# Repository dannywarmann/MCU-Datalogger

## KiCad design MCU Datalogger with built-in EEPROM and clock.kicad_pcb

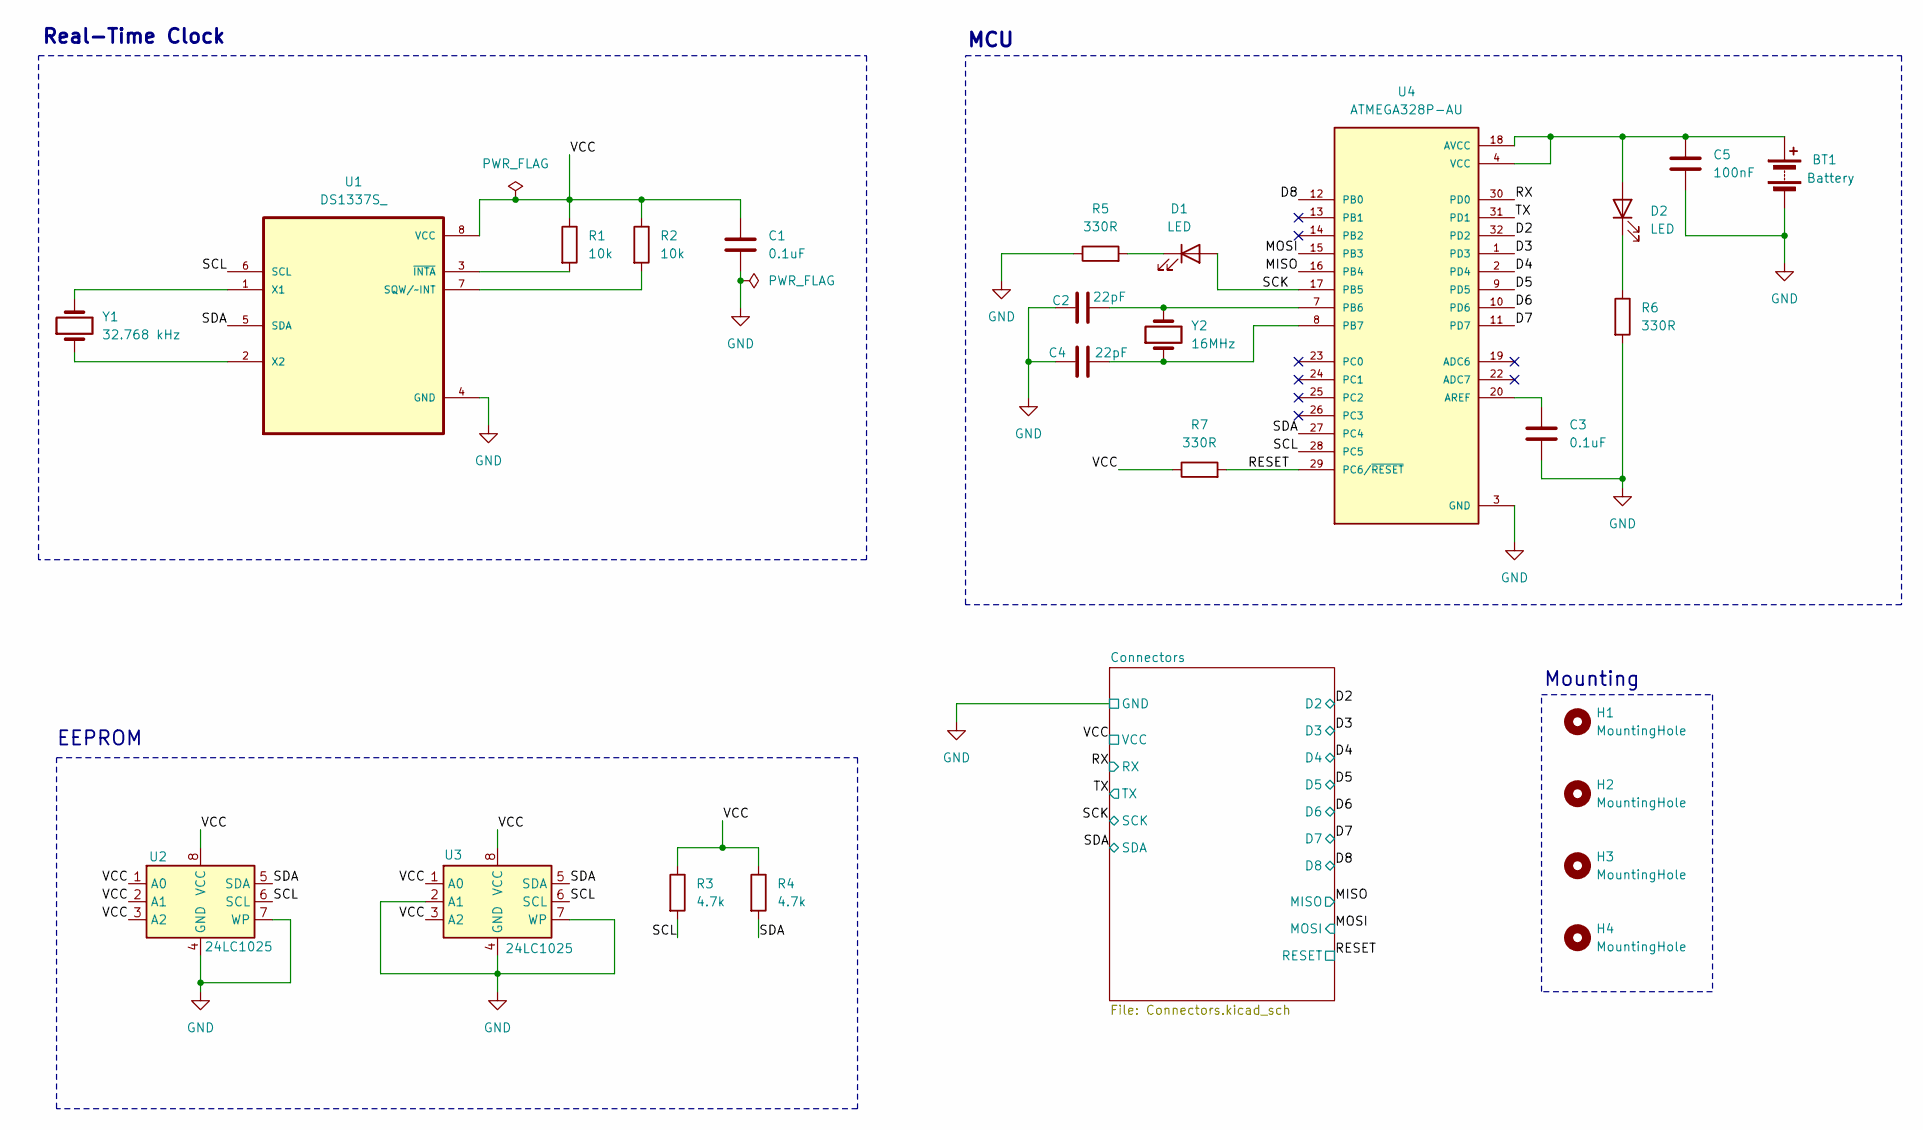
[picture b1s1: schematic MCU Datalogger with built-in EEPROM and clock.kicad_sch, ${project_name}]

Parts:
BT1: Battery; PinHeader_1x02_P2.54mm_Vertical
C1, C3: 0.1uF; C_0805_2012Metric
C2, C4: 22pF; C_0805_2012Metric
C5: 100nF; C_0805_2012Metric
D1, D2: LED; LED_0805_2012Metric
H1, H2, H3, H4: MountingHole; MountingHole_2.1mm
R1, R2: 10k; R_0805_2012Metric
R3, R4: 4.7k; R_0805_2012Metric
R5, R6, R7: 330R; R_0805_2012Metric
U1: DS1337S_; SOIC127P600X175-8N
U2, U3: 24LC1025; SOIC-8_5.3x5.3mm_P1.27mm
U4: ATMEGA328P-AU; QFP80P900X900X120-32N; PARTREV 8271A
Y1: 32.768 kHz; Crystal_SMD_5032-2Pin_5.0x3.2mm
Y2: 16MHz; Crystal_SMD_5032-2Pin_5.0x3.2mm

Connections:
/D2: U4.32 (PD2); also elsewhere on the board
/D3: U4.1 (PD3); also elsewhere on the board
/D4: U4.2 (PD4); also elsewhere on the board
/D5: U4.9 (PD5); also elsewhere on the board
/D6: U4.10 (PD6); also elsewhere on the board
/D7: U4.11 (PD7); also elsewhere on the board
/D8: U4.12 (PB0); also elsewhere on the board
/MISO: U4.16 (PB4); also elsewhere on the board
/MOSI: U4.15 (PB3); also elsewhere on the board
/RESET: R7.2, U4.29 (PC6/~RESET); also elsewhere on the board
/RX: U4.30 (PD0); also elsewhere on the board
/SCK: D1.2 (A), U4.17 (PB5); also elsewhere on the board
/SCL: R3.2, U1.6 (SCL), U2.6 (SCL), U3.6 (SCL), U4.28 (PC5)
/SDA: R4.2, U1.5 (SDA), U2.5 (SDA), U3.5 (SDA), U4.27 (PC4); also elsewhere on the board
/TX: U4.31 (PD1); also elsewhere on the board
GND: BT1.2 (-), C1.2, C2.1, C3.2, C4.1, C5.2, R5.1, R6.2, U1.4 (GND), U2.4 (GND), U2.7 (WP), U3.2 (A1), U3.4 (GND), U3.7 (WP), U4.3 (GND), U4.5 (GND), U4.21 (GND); also elsewhere on the board
unnamed: D1.1 (K), R5.2
unnamed: D2.1 (K), R6.1
unnamed: R2.2, U1.7 (SQW/~INT)
unnamed: U1.1 (X1), Y1.2
unnamed: U1.2 (X2), Y1.1
unnamed: R1.2, U1.3 (~INTA)
unnamed: C3.1, U4.20 (AREF)
unnamed: C2.2, U4.7 (PB6), Y2.2
unnamed: C4.2, U4.8 (PB7), Y2.1

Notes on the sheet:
Real-Time Clock
MCU
EEPROM
Mounting

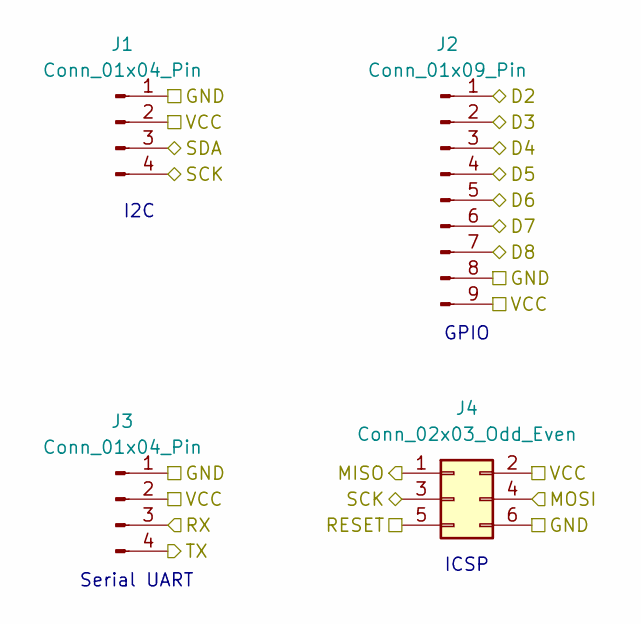
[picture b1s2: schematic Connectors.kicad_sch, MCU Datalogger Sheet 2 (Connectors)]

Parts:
J1, J3: Conn_01x04_Pin; PinHeader_1x04_P2.54mm_Vertical
J2: Conn_01x09_Pin; PinHeader_1x09_P2.54mm_Vertical
J4: Conn_02x03_Odd_Even; PinHeader_2x03_P2.54mm_Vertical

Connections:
/D2: J2.1; also elsewhere on the board
/D3: J2.2; also elsewhere on the board
/D4: J2.3; also elsewhere on the board
/D5: J2.4; also elsewhere on the board
/D6: J2.5; also elsewhere on the board
/D7: J2.6; also elsewhere on the board
/D8: J2.7; also elsewhere on the board
/MISO: J4.1; also elsewhere on the board
/MOSI: J4.4; also elsewhere on the board
/RESET: J4.5; also elsewhere on the board
/RX: J3.3; also elsewhere on the board
/SCK: J1.4, J4.3; also elsewhere on the board
/SDA: J1.3; also elsewhere on the board
/TX: J3.4; also elsewhere on the board
GND: J1.1, J2.8, J3.1, J4.6; also elsewhere on the board

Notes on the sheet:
I2C
GPIO
Serial UART
ICSP

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
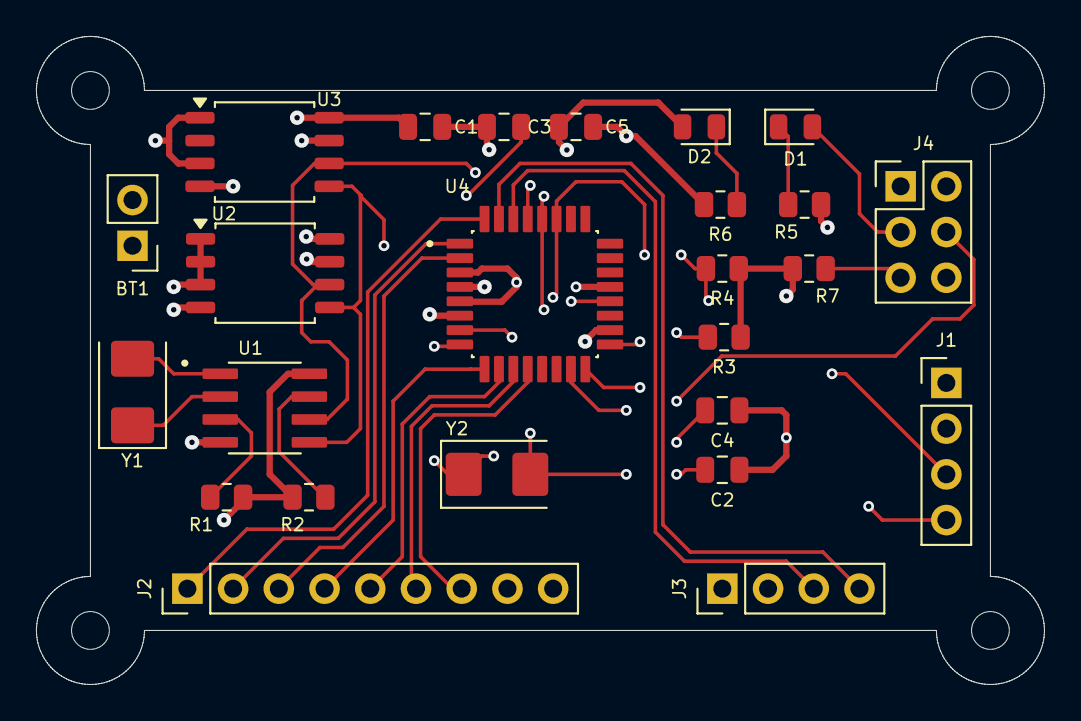
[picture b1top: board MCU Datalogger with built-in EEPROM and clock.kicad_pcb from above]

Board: 4 copper layers, 56.0 x 36.0 mm, 29 parts (0 on the bottom side), 26 nets.
